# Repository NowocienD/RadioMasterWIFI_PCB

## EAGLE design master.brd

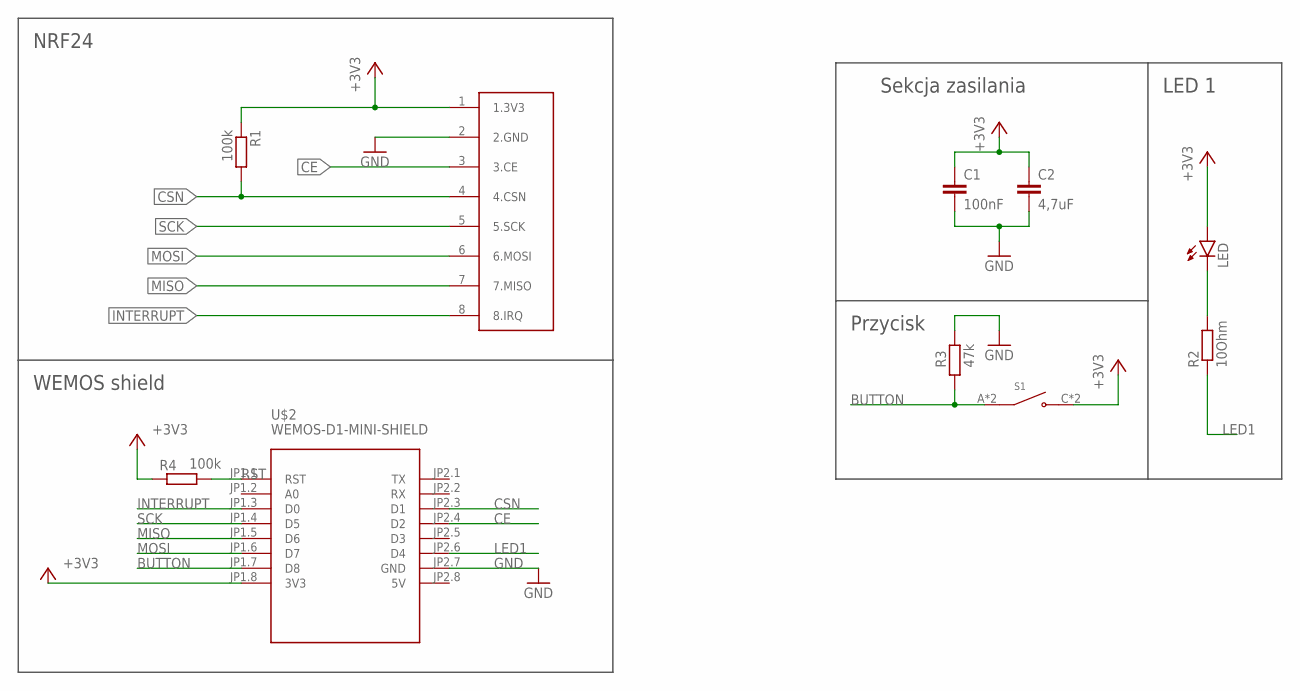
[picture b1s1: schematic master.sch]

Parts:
C1: 100nF; C0805
C2: 4,7uF; C025-050X050
LED: LEDCHIP-LED0805; CHIP-LED0805
NRF24: NRF24L01+
R1, R4: 100k; M0805
R2: 10Ohm; M0805
R3: 47k; M0805
S1: TS-1187A-B-A-B; SW_TS-1187A-B-A-B
U$2: WEMOS-D1-MINI-SHIELD

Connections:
5V: U$2.JP2.8 (5V)
+3V3: C1.1, C2.1, LED.A, NRF24.1 (1.3V3), R1.1, R4.1, S1.C (NO), S1.D (NO), U$2.JP1.8 (3V3)
BUTTON: R3.1, S1.A (COM), S1.B (COM), U$2.JP1.7 (D8)
CE: NRF24.3 (3.CE), U$2.JP2.4 (D2)
CSN: NRF24.4 (4.CSN), R1.2, U$2.JP2.3 (D1)
GND: C1.2, C2.2, NRF24.2 (2.GND), R3.2, U$2.JP2.7 (GND)
INTERRUPT: NRF24.8 (8.IRQ), U$2.JP1.3 (D0)
LED1: R2.1, U$2.JP2.6 (D4)
MISO: NRF24.7 (7.MISO), U$2.JP1.5 (D6)
MOSI: NRF24.6 (6.MOSI), U$2.JP1.6 (D7)
unnamed: LED.C, R2.2
RST: R4.2, U$2.JP1.1 (RST)
SCK: NRF24.5 (5.SCK), U$2.JP1.4 (D5)

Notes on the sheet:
Sekcja zasilania
NRF24
Przycisk
LED 1
WEMOS shield

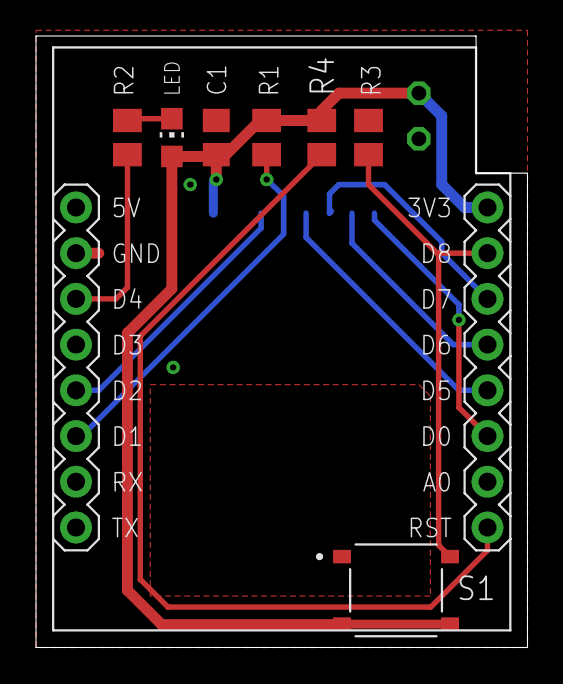
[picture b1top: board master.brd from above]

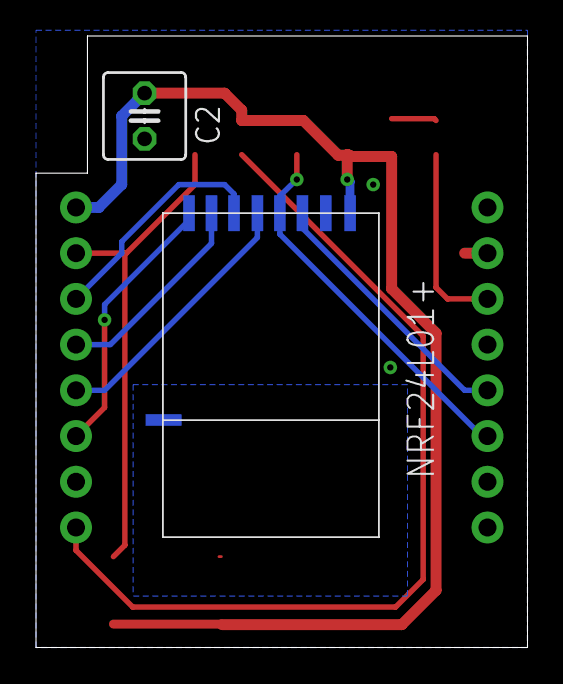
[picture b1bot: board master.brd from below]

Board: 2 copper layers, 27.3 x 34.0 mm, 10 parts (2 on the bottom side), 12 nets.

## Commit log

2020-11-24 wersja do druku
2020-12-27 poprawione polaczenia, usunieta masa pod antena,
2020-12-28 dodanei warstwy opisowej do panelizacji
2021-01-02 drobne poprawki

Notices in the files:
parts and their libraries:
diy-modules: Released under the Creative Commons Attribution 4.0 International License: http://creativecommons.org/licenses/by/4.0
